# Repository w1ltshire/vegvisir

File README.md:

# `vegvisir`

---

## Purpose of this project
I've been into unmanned vehicles a little bit of time. This project is my attempt at making a full and simple
software/hardware complex of an unmanned surface vessel.

## Naming
As I'm aiming to make basically an autopilot for a drone, it was named appropriately.<br/>
From Wikipedia:
> The **vegvísir** is an Icelandic magical stave intended to help the bearer find their way through rough weather.

## Documentation
For extended information about crates, refer to their relevant READMEs.

## License
[MIT](https://choosealicense.com/licenses/mit/)

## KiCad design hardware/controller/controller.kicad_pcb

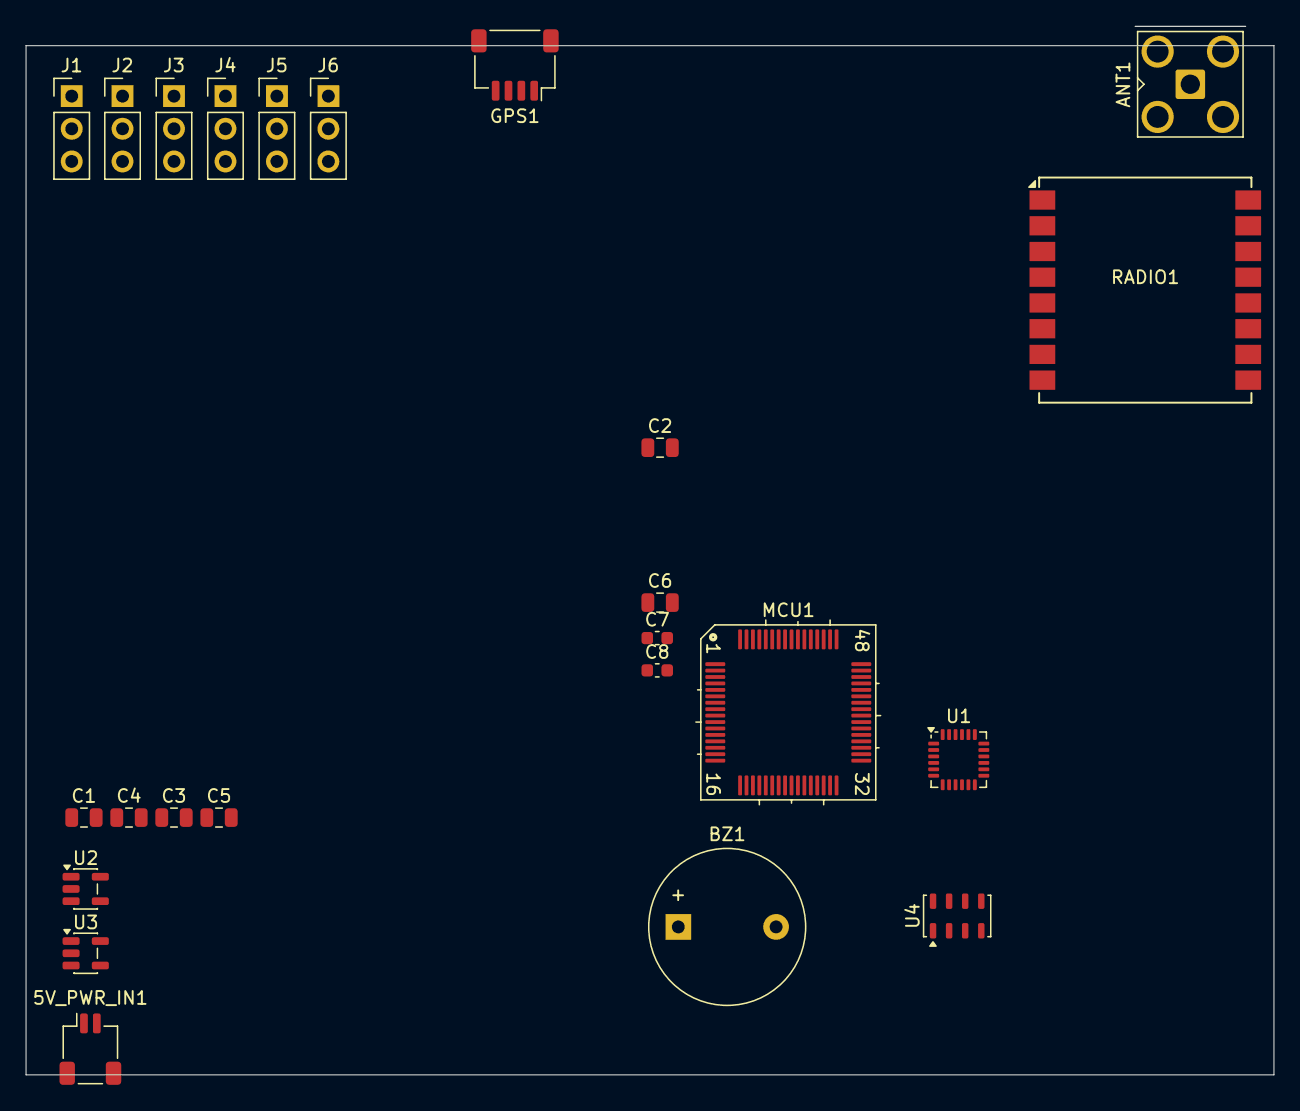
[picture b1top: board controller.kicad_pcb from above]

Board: 2 copper layers, 97.0 x 81.5 mm, 24 parts (0 on the bottom side), 27 nets, no tracks yet.

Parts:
5V_PWR_IN1: Conn_01x02_Socket; JST_SH_SM02B-SRSS-TB_1x02-1MP_P1.00mm_Horizontal
ANT1: Conn_Coaxial; SMA_Amphenol_901-143_Horizontal
BZ1: Buzzer; Buzzer_12x9.5RM7.6
C1, C3, C4, C5: C; C_0805_2012Metric
C2: 4.7uF; C_0805_2012Metric
C6: 2.2nF; C_0805_2012Metric
C7, C8: 0.1uF; C_0603_1608Metric
GPS1: Conn_01x04_Socket; JST_SH_SM04B-SRSS-TB_1x04-1MP_P1.00mm_Horizontal
J1, J2, J3, J4, J5, J6: Conn_01x03_Pin; PinHeader_1x03_P2.54mm_Vertical
MCU1: STM32F401RETx; LQFP-64_10x10mm_P0.5mm
RADIO1: Ai-Thinker-Ra-01; Ai-Thinker-Ra-01-LoRa
U1: MPU-6050; InvenSense_QFN-24_4x4mm_P0.5mm
U2: TLV70030_SOT23-5; SOT-23-5
U3: TLV70018_SOT23-5; SOT-23-5
U4: MPL115A1; NXP_LGA-8_3x5mm_P1.25mm_H1.2mm

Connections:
+1V8: C5.2, U1.8 (VLOGIC), U3.5 (OUT)
+3.3V: C1.2, MCU1.13 (VREF+), MCU1.19 (VDD), MCU1.32 (VDD), MCU1.48 (VDD), MCU1.64 (VDD), RADIO1.3 (VDD), U1.13 (VDD), U2.5 (OUT), U4.1 (VDD)
+5V: 5V_PWR_IN1.1, C3.2, C4.2, GPS1.1, J1.2, J2.2, J3.2, J4.2, J5.2, J6.2, U2.1 (IN), U2.3 (EN), U3.1 (IN), U3.3 (EN)
EXTI0: MCU1.26 (PB0), RADIO1.5 (DIO0)
EXTI1: MCU1.27 (PB1), U1.12 (INT)
GND: 5V_PWR_IN1.2, ANT1.2 (Ext), BZ1.2 (-), C1.1, C2.2, C3.1, C4.1, C5.1, C6.2, C7.2, C8.2, GPS1.4, J1.1, J2.1, J3.1, J4.1, J5.1, J6.1, MCU1.12 (VSSA), MCU1.18 (VSS), MCU1.31 (VSS), MCU1.47 (VSS), MCU1.63 (VSS), RADIO1.2 (GND), RADIO1.9 (GND), RADIO1.16 (GND), U1.9 (AD0), U1.18 (GND), U2.2 (GND), U3.2 (GND), U4.3 (GND)
I2C1_SCL: MCU1.61 (PB8), U1.23 (SCL)
I2C1_SDA: MCU1.62 (PB9), U1.24 (SDA)
unnamed: ANT1.1 (In), RADIO1.1 (ANT)
unnamed: BZ1.1 (+), MCU1.54 (PD2)
unnamed: C2.1, MCU1.30 (VCAP1)
unnamed: C6.1, U1.20 (CPOUT)
unnamed: C7.1, U1.10 (REGOUT)
unnamed: C8.1, U4.2 (CAP)
PWM2/1: J1.3, MCU1.50 (PA15)
PWM2/2: J2.3, MCU1.15 (PA1)
PWM3/1: J3.3, MCU1.37 (PC6)
PWM3/2: J4.3, MCU1.38 (PC7)
PWM3/3: J5.3, MCU1.39 (PC8)
PWM4/2: J6.3, MCU1.59 (PB7)
RST0: MCU1.58 (PB6), RADIO1.4 (~RESET)
SPI1_MISO: MCU1.56 (PB4), RADIO1.13 (MISO)
SPI1_MOSI: MCU1.57 (PB5), RADIO1.14 (MOSI)
SPI1_NSS: MCU1.28 (PB2), RADIO1.15 (~NSS)
SPI1_SCLK: MCU1.55 (PB3), RADIO1.12 (SCK)
UART1_RX: GPS1.3, MCU1.43 (PA10)
UART1_TX: GPS1.2, MCU1.42 (PA9)

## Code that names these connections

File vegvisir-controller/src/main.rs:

#![cfg_attr(not(doctest), doc = include_str!("../README.md"))]
#![no_std]
#![no_main]

mod drivers;
mod phy;

use defmt::info;
use crate::drivers::gps::GPSDriver;
use embassy_executor::Spawner;
use embassy_stm32::{bind_interrupts, interrupt, peripherals, spi, usart};
use embassy_stm32::gpio::{Level, Output, Pull, Speed};
use embassy_stm32::exti::{self, ExtiInput};
use embassy_stm32::time::khz;
use embassy_time::Delay;
use embedded_hal_bus::spi::ExclusiveDevice;
#[allow(unused_imports)]
use {defmt_rtt as _, panic_probe as _};
use lora_phy::iv::GenericSx127xInterfaceVariant;
use lora_phy::sx127x::{Sx1276, Sx127x};
use lora_phy::LoRa;
use lora_phy::{mod_params::*, sx127x};

bind_interrupts!(struct Irqs {
    USART1 => usart::BufferedInterruptHandler<peripherals::USART1>;
    EXTI0 => exti::InterruptHandler<interrupt::typelevel::EXTI0>;
});

const LORA_FREQUENCY_IN_HZ: u32 = 433_000_000; // warning: set this appropriately for the region

#[embassy_executor::main]
async fn main(spawner: Spawner) {
    let mut config = embassy_stm32::Config::default();
    config.rcc.hsi = true;
    config.rcc.sys = embassy_stm32::rcc::Sysclk::HSI;
    let p = embassy_stm32::init(config);

    let nss = Output::new(p.PB2, Level::High, Speed::Low);
    let reset = Output::new(p.PB1, Level::High, Speed::Low);
    let irq = ExtiInput::new(p.PB0, p.EXTI0, Pull::Up, Irqs);

    info!("Trans Rights are Human Rights!");
    let mut spi_cfg = spi::Config::default();
    spi_cfg.frequency = khz(200);
    let spi = spi::Spi::new(
        p.SPI1,
        p.PB3,
        p.PB5,
        p.PB4,
        p.DMA2_CH3,
        p.DMA2_CH2,
        spi_cfg,
    );

    let spi = ExclusiveDevice::new(spi, nss, Delay).unwrap();

    let config = sx127x::Config {
        chip: Sx1276,
        tcxo_used: true,
        rx_boost: false,
        tx_boost: true,
    };
    let iv = GenericSx127xInterfaceVariant::new(reset, irq, None, None).unwrap();
    let mut lora = LoRa::new(Sx127x::new(spi, iv, config), false, Delay).await.unwrap();

    let mdltn_params = {
        match lora.create_modulation_params(
            SpreadingFactor::_10,
            Bandwidth::_250KHz,
            CodingRate::_4_8,
            LORA_FREQUENCY_IN_HZ,
        ) {
            Ok(mp) => mp,
            Err(err) => {
                info!("Radio error = {}", err);
                return;
            }
        }
    };

    let mut tx_pkt_params = {
        match lora.create_tx_packet_params(4, false, true, false, &mdltn_params) {
            Ok(pp) => pp,
            Err(err) => {
                info!("Radio error = {}", err);
                return;
            }
        }
    };

    let buffer = [0x01u8, 0x02u8, 0x03u8];

    match lora
        .prepare_for_tx(&mdltn_params, &mut tx_pkt_params, 20, &buffer)
        .await
    {
        Ok(()) => {}
        Err(err) => {
            info!("Radio error = {}", err);
            return;
        }
    };

    match lora.tx().await {
        Ok(()) => {
            info!("TX DONE");
        }
        Err(err) => {
            info!("Radio error = {}", err);
            return;
        }
    };

    match lora.sleep(false).await {
        Ok(()) => info!("Sleep successful"),
        Err(err) => info!("Sleep unsuccessful = {}", err),
    }

    // TODO: improve error handling (send over lora? do some freaky stuff like blink an led or buzz?)
    GPSDriver::new(p.USART1, p.PA10, p.PA9, 9600).spawn(&spawner).unwrap();
}

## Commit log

2026-03-09 initial commit
    added:
    * test uart reading in `vegvisir-mcu`
    * nmea-0183 sentences parsing via `nmea` crate
2026-03-09 chore: rename `vegvisir-mcu` to `vegvisir-controller`
2026-03-09 feat: `buffered_uart` macro
    added this macro so it is somewhat easier to modify uart pins if they differ
2026-03-09 chore: `build_and_flash.sh`
    reason for adding this script are described in it
2026-03-09 docs: README
2026-03-09 feat: `drivers` and `phy` modules
    changed:
    * moved out gps to `drivers` module
    * moved out uart to `phy`
2026-03-09 feat: return `panic_probe`
2026-03-09 docs: change comments to rustdoc
2026-03-09 chore: add license
2026-03-09 feat: improve error handling
2026-03-09 docs: add README for vegvisir-controller
2026-03-09 feat: `NmeaLine` for convenience
2026-03-10 docs: girl why you so cheerful
2026-03-10 feat!: change drivers a little
    changed:
    * drivers are now represented by structs
    * driver structs must have a spawn function
    * driver tasks are now spawned via the aforementioned function
2026-03-10 feat!: change `GPSDriver::new` signature and method of creating it
    changed:
    * take `Peri<'static, T>`, `Peri<'static, impl RxPin<T>>`, `Peri<'static, impl TxPin<T>>` (similarly to BufferedUart::new)
    * change `buffered_uart!` macro parameters
2026-03-10 chore: formatting
2026-03-11 fix: import required structs in `buffered_uart!`
2026-03-11 docs(uart): update
2026-03-12 feat(drivers): `Driver` trait
2026-03-12 feat: `vegvisir-protocol` stub
2026-03-13 feat(protocol): `Packet` structure stub
    added:
    * `Packet` struct
    * a simple serialization test for it
2026-03-13 docs: ugh that sounded weird tbh
2026-03-13 docs(drivers): add docs for `DriverError`
2026-03-13 feat!: revert `Driver` trait
2026-03-13 feat: change `GPSDriver` invocation
2026-03-13 feat(drivers): improve error handling
2026-03-13 fix: warnings
2026-03-14 feat(protocol): `Packet::serialize`
2026-03-14 feat(protocol): error handling, `from_slice` and `from_vec`
2026-03-14 tests(protocol): test for `Packet::from_slice`, add assertions
2026-03-14 feat(protocol): `Message`
2026-03-14 feat: `vegvisir-crypto` stub
2026-03-14 fix: rustdoc warning (unclosed tag)
2026-03-14 chore(package): add `license`, `repository`, `description`
2026-03-14 chore: remove unused dependency
2026-03-14 feat: add `vegvisir-transport` stub crate
2026-03-14 feat(transport): add `Transport` trait
2026-03-14 feat(crypto): use `snow`, add `MockTransport` and session test
2026-03-15 feat(transport): `Listener` trait
2026-03-15 feat(transport): basic tcp
2026-03-16 chore: guess who got a new board
2026-03-22 feat: `TCPClient::new`, change return type for `TCPServer::accept`
2026-03-28 feat: start rewriting gcs... controls......,,
2026-04-01 feat: lora stub
2026-04-05 feat: initial pcb commit
2026-04-16 feat: gcs ui stub
2026-04-16 chore: gcs package
